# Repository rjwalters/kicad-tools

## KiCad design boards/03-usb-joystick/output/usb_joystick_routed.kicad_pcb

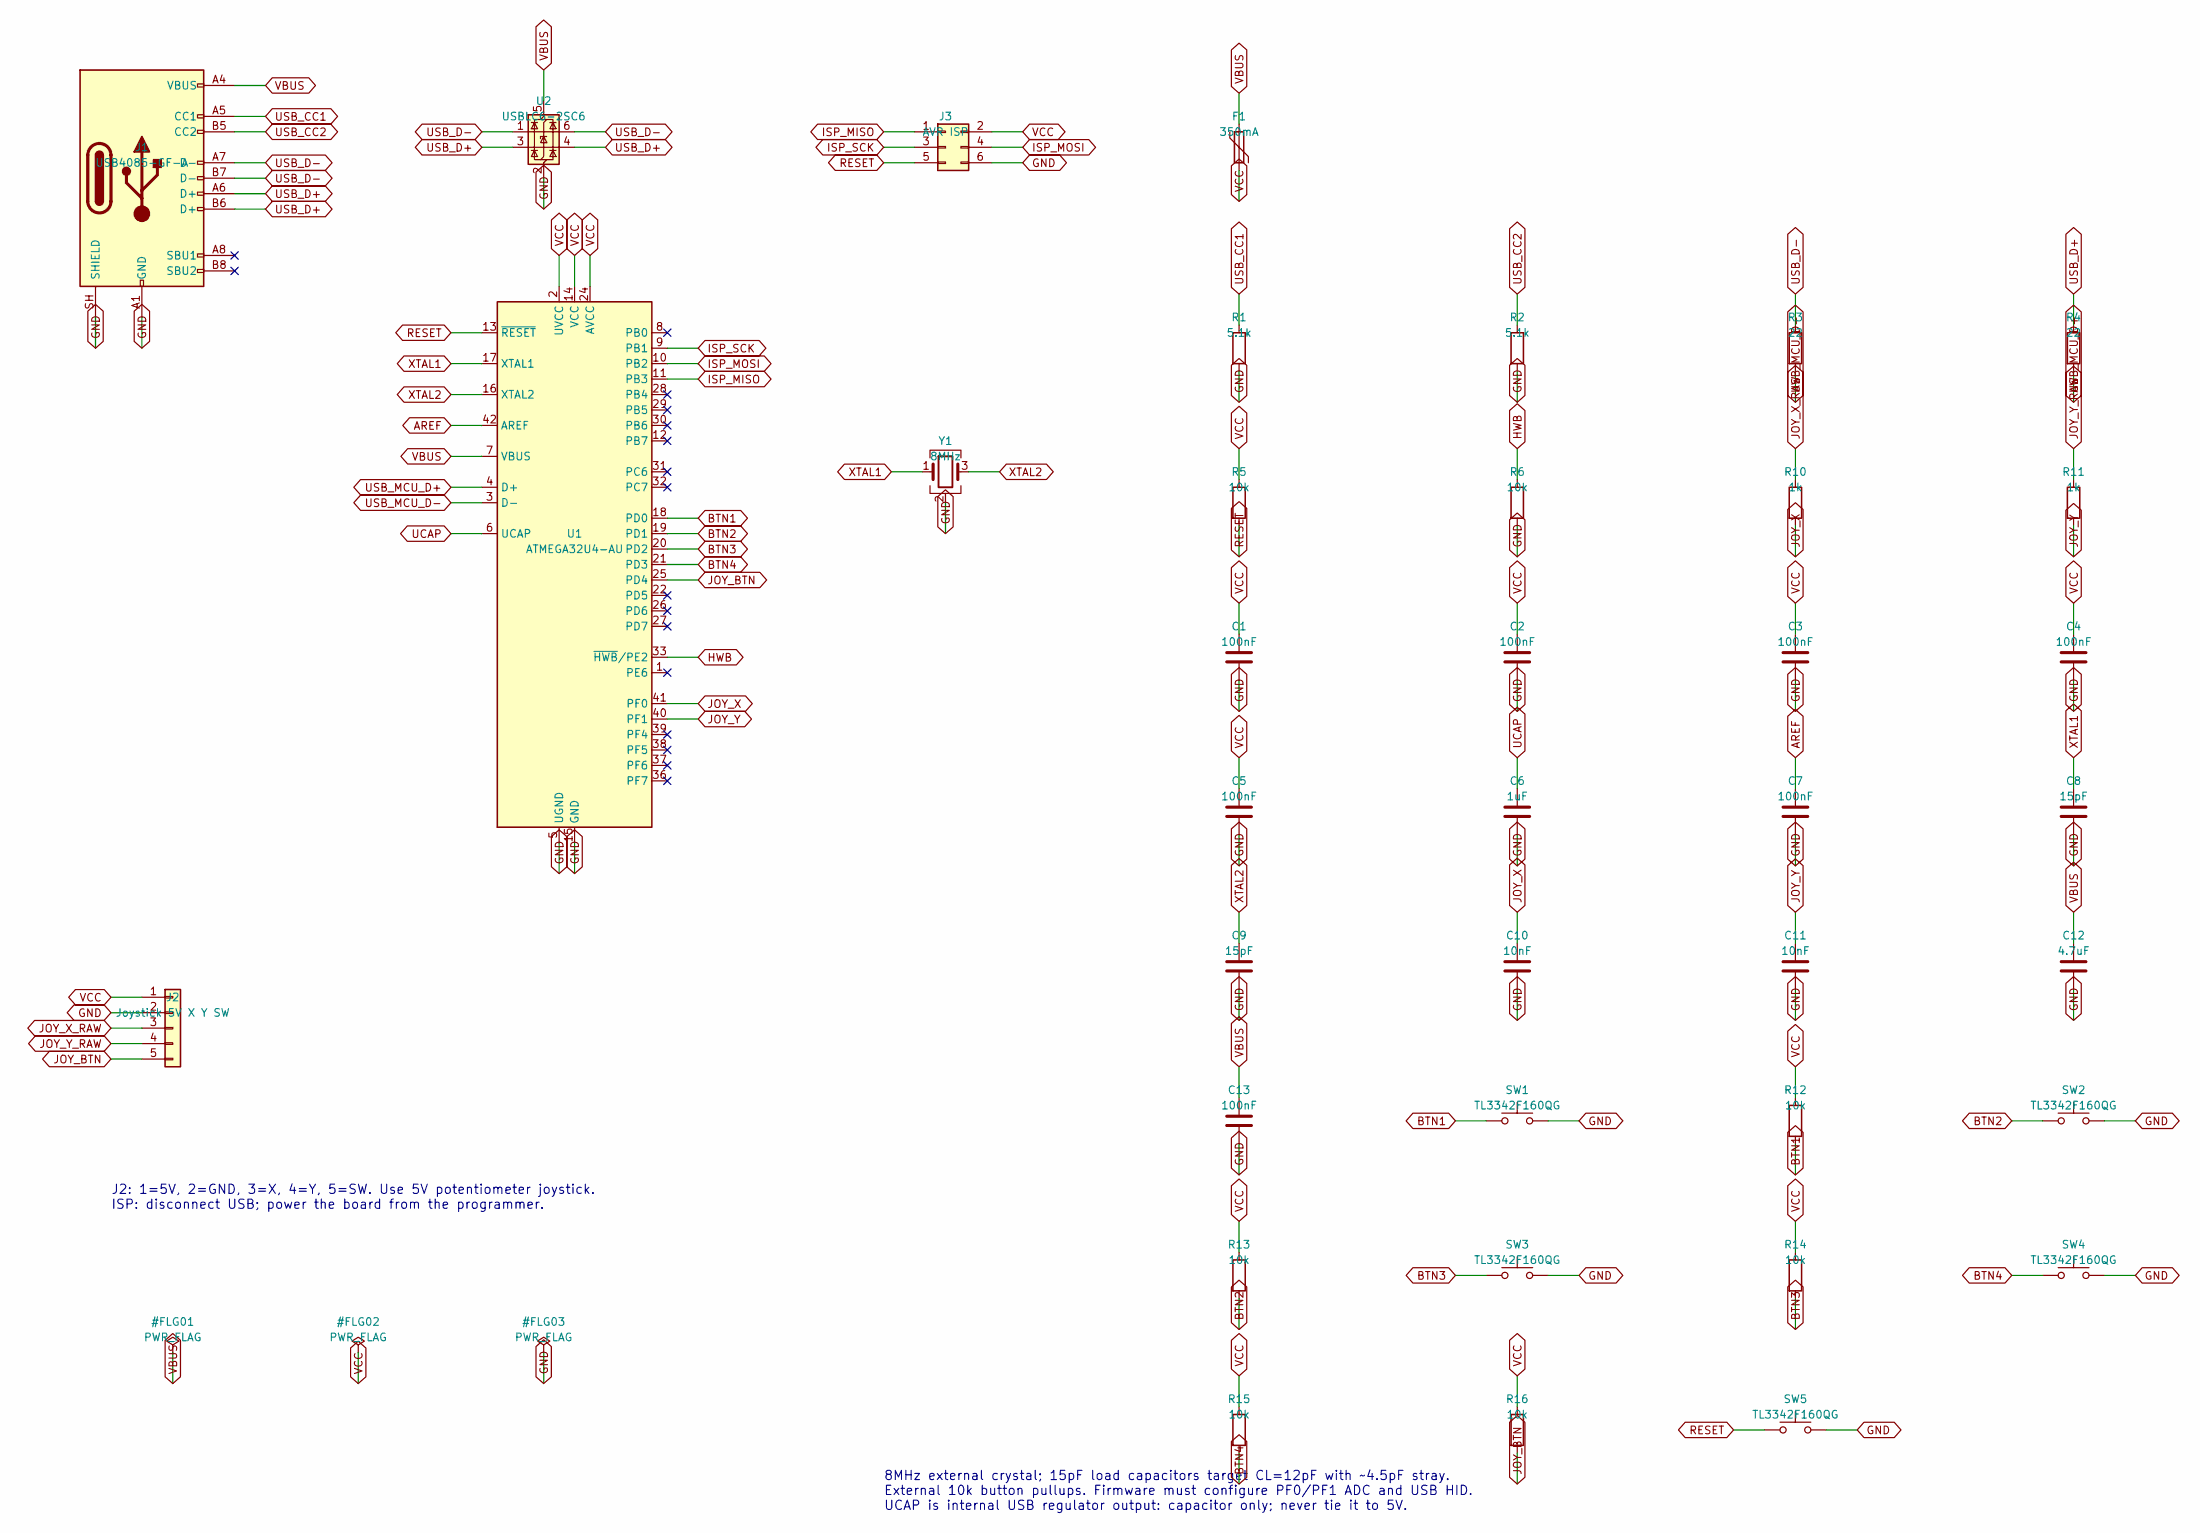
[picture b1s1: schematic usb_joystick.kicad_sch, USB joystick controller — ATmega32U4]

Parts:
C1, C2, C3, C4, C5, C7, C13: 100nF; C_0603_1608Metric; MPN GRM188R71C104KA01D; LCSC C45000
C6: 1uF; C_0603_1608Metric; MPN GRM188R71A105KA61D; LCSC C97888
C8, C9: 15pF; C_0603_1608Metric; MPN GRM1885C1H150JA01D; LCSC C71651
C10, C11: 10nF; C_0603_1608Metric; MPN GRM188R71H103KA01D; LCSC C77053
C12: 4.7uF; C_0603_1608Metric; MPN GRM188R61A475KE15D; LCSC C71633
F1: 350mA; Fuse_1206_3216Metric; MPN 1206L035/16YR; LCSC C126817
J1: USB4085-GF-A; USB_C_Receptacle_GCT_USB4085; MPN USB4085-GF-A; LCSC C7095263
J2: Joystick 5V X Y SW; JST_PH_S5B-PH-SM4-TB_1x05-1MP_P2.00mm_Horizontal; MPN S5B-PH-SM4-TB(LF)(SN); LCSC C265104
J3: AVR ISP; Samtec_TSM-103-01-T-DV; MPN TSM-103-01-T-DV-P-TR; LCSC C21285200
R1, R2: 5.1k; R_0603_1608Metric; MPN RC0603FR-075K1L; LCSC C105580
R3, R4: 22; R_0402_1005Metric; MPN RC0402FR-0722RL; LCSC C114765
R5, R6, R12, R13, R14, R15, R16: 10k; R_0603_1608Metric; MPN RC0603FR-0710KL; LCSC C98220
R10, R11: 1k; R_0603_1608Metric; MPN RC0603FR-071KL; LCSC C22548
SW1, SW2, SW3, SW4, SW5: TL3342F160QG; SW_SPST_TL3342; MPN TL3342F160QG; LCSC C2886898
U1: ATMEGA32U4-AU; TQFP-44_10x10mm_P0.8mm; MPN ATMEGA32U4-AU; LCSC C44854
U2: USBLC6-2SC6; SOT-23-6; MPN USBLC6-2SC6; LCSC C7519
Y1: 8MHz; Crystal_SMD_3225-4Pin_3.2x2.5mm; MPN ECS-80-12-33-JGN-TR; LCSC C2442665

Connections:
AREF: C7.1, U1.42 (AREF)
BTN1: R12.2, SW1.1, U1.18 (PD0)
BTN2: R13.2, SW2.1, U1.19 (PD1)
BTN3: R14.2, SW3.1, U1.20 (PD2)
BTN4: R15.2, SW4.1, U1.21 (PD3)
GND: C1.2, C2.2, C3.2, C4.2, C5.2, C6.2, C7.2, C8.2, C9.2, C10.2, C11.2, C12.2, C13.2, J1.A1 (GND), J1.A12 (GND), J1.B1 (GND), J1.B12 (GND), J1.SH (SHIELD), J2.2, J3.6, R1.2, R2.2, R6.2, SW1.2, SW2.2, SW3.2, SW4.2, SW5.2, U1.5 (UGND), U1.15 (GND), U1.23 (GND), U1.35 (GND), U1.43 (GND), U2.2 (GND), Y1.2 (G), Y1.4 (G)
HWB: R6.1, U1.33 (~HWB/PE2)
ISP_MISO: J3.1, U1.11 (PB3)
ISP_MOSI: J3.4, U1.10 (PB2)
ISP_SCK: J3.3, U1.9 (PB1)
JOY_BTN: J2.5, R16.2, U1.25 (PD4)
JOY_X: C10.1, R10.2, U1.41 (PF0)
JOY_X_RAW: J2.3, R10.1
JOY_Y: C11.1, R11.2, U1.40 (PF1)
JOY_Y_RAW: J2.4, R11.1
RESET: J3.5, R5.2, SW5.1, U1.13 (~RESET)
UCAP: C6.1, U1.6 (UCAP)
USB_CC1: J1.A5 (CC1), R1.1
USB_CC2: J1.B5 (CC2), R2.1
USB_D+: J1.A6 (D+), J1.B6 (D+), R4.1, U2.3 (I/O2), U2.4 (I/O2)
USB_D-: J1.A7 (D-), J1.B7 (D-), R3.1, U2.1 (I/O1), U2.6 (I/O1)
USB_MCU_D+: R4.2, U1.4 (D+)
USB_MCU_D-: R3.2, U1.3 (D-)
VBUS: C12.1, C13.1, F1.1, J1.A4 (VBUS), J1.A9 (VBUS), J1.B4 (VBUS), J1.B9 (VBUS), U1.7 (VBUS), U2.5 (VBUS)
VCC: C1.1, C2.1, C3.1, C4.1, C5.1, F1.2, J2.1, J3.2, R5.1, R12.1, R13.1, R14.1, R15.1, R16.1, U1.2 (UVCC), U1.14 (VCC), U1.24 (AVCC), U1.34 (VCC), U1.44 (AVCC)
XTAL1: C8.1, U1.17 (XTAL1), Y1.1
XTAL2: C9.1, U1.16 (XTAL2), Y1.3

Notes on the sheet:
J2: 1=5V, 2=GND, 3=X, 4=Y, 5=SW. Use 5V potentiometer joystick. ISP: disconnect USB; power the board from the programmer.
8MHz external crystal; 15pF load capacitors target CL=12pF with ~4.5pF stray. External 10k button pullups. Firmware must configure PF0/PF1 ADC and USB HID. UCAP is internal USB regulator output: capacitor only; never tie it to 5V.

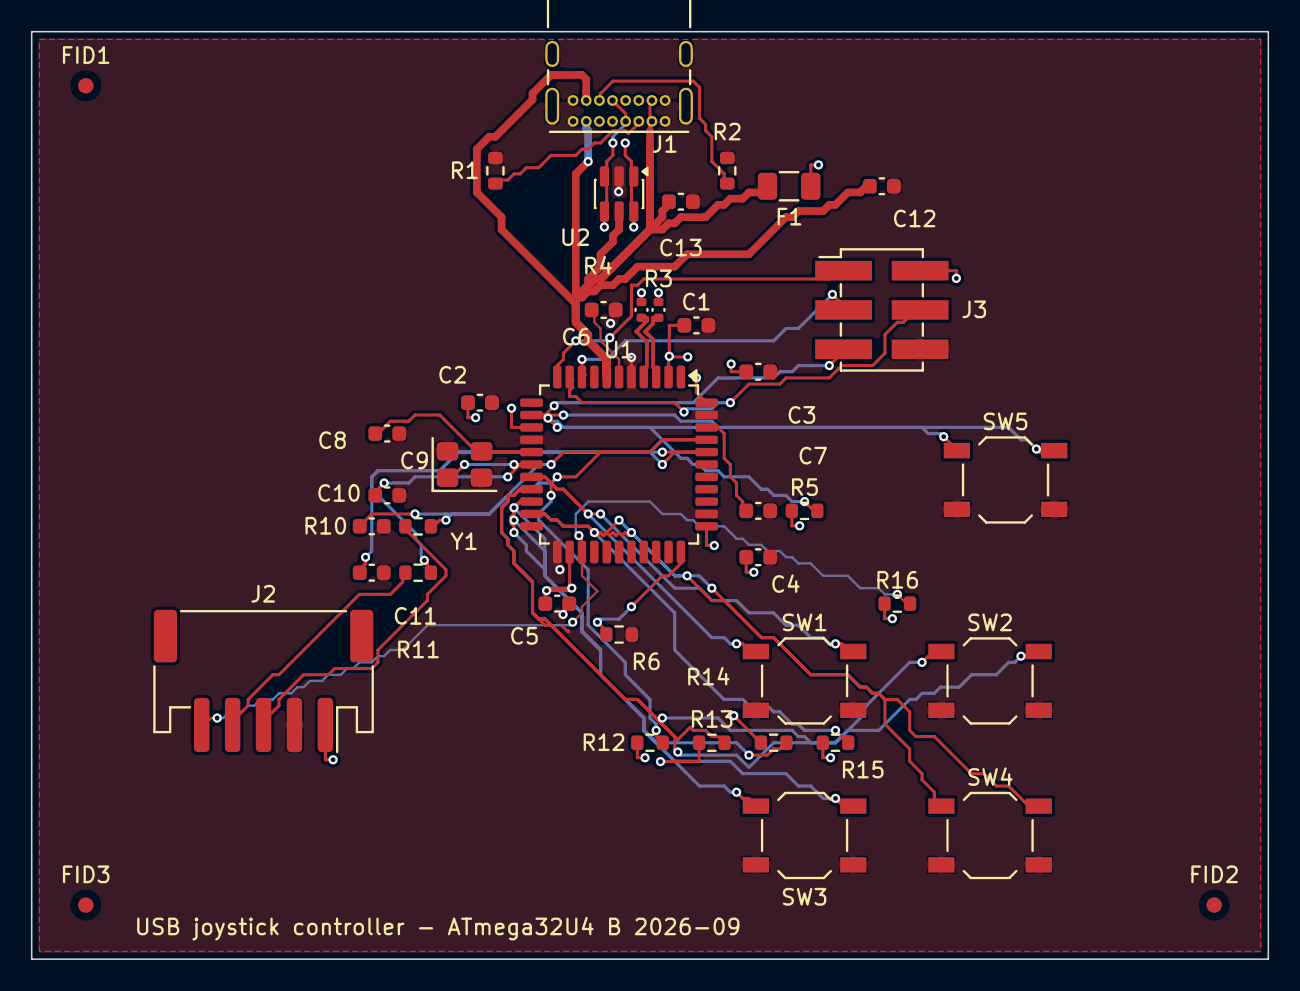
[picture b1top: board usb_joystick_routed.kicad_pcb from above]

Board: 4 copper layers, 80.0 x 60.0 mm, 41 parts (0 on the bottom side), 27 nets.

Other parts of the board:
FID1, FID2, FID3: Fiducial; Fiducial_1mm_Mask2mm

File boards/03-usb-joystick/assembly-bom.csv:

Reference,Value,Manufacturer,MPN,Footprint
U1,ATMEGA32U4-AU,Microchip,ATMEGA32U4-AU,Package_QFP:TQFP-44_10x10mm_P0.8mm
J1,USB4085-GF-A,GCT,USB4085-GF-A,Connector_USB:USB_C_Receptacle_GCT_USB4085
U2,USBLC6-2SC6,STMicroelectronics,USBLC6-2SC6,Package_TO_SOT_SMD:SOT-23-6
F1,350mA,Littelfuse,1206L035/16YR,Fuse:Fuse_1206_3216Metric
Y1,8MHz,ECS,ECS-80-12-33-JGN-TR,Crystal:Crystal_SMD_3225-4Pin_3.2x2.5mm
J2,Joystick 5V X Y SW,JST,S5B-PH-SM4-TB(LF)(SN),Connector_JST:JST_PH_S5B-PH-SM4-TB_1x05-1MP_P2.00mm_Horizontal
J3,AVR ISP,Samtec,TSM-103-01-T-DV-P-TR,Joystick:Samtec_TSM-103-01-T-DV
R1,5.1k,Yageo,RC0603FR-075K1L,Resistor_SMD:R_0603_1608Metric
R2,5.1k,Yageo,RC0603FR-075K1L,Resistor_SMD:R_0603_1608Metric
R3,22,Yageo,RC0402FR-0722RL,Resistor_SMD:R_0402_1005Metric
R4,22,Yageo,RC0402FR-0722RL,Resistor_SMD:R_0402_1005Metric
R5,10k,Yageo,RC0603FR-0710KL,Resistor_SMD:R_0603_1608Metric
R6,10k,Yageo,RC0603FR-0710KL,Resistor_SMD:R_0603_1608Metric
R10,1k,Yageo,RC0603FR-071KL,Resistor_SMD:R_0603_1608Metric
R11,1k,Yageo,RC0603FR-071KL,Resistor_SMD:R_0603_1608Metric
C1,100nF,Murata,GRM188R71C104KA01D,Capacitor_SMD:C_0603_1608Metric
C2,100nF,Murata,GRM188R71C104KA01D,Capacitor_SMD:C_0603_1608Metric
C3,100nF,Murata,GRM188R71C104KA01D,Capacitor_SMD:C_0603_1608Metric
C4,100nF,Murata,GRM188R71C104KA01D,Capacitor_SMD:C_0603_1608Metric
C5,100nF,Murata,GRM188R71C104KA01D,Capacitor_SMD:C_0603_1608Metric
C6,1uF,Murata,GRM188R71A105KA61D,Capacitor_SMD:C_0603_1608Metric
C7,100nF,Murata,GRM188R71C104KA01D,Capacitor_SMD:C_0603_1608Metric
C8,15pF,Murata,GRM1885C1H150JA01D,Capacitor_SMD:C_0603_1608Metric
C9,15pF,Murata,GRM1885C1H150JA01D,Capacitor_SMD:C_0603_1608Metric
C10,10nF,Murata,GRM188R71H103KA01D,Capacitor_SMD:C_0603_1608Metric
C11,10nF,Murata,GRM188R71H103KA01D,Capacitor_SMD:C_0603_1608Metric
C12,4.7uF,Murata,GRM188R61A475KE15D,Capacitor_SMD:C_0603_1608Metric
C13,100nF,Murata,GRM188R71C104KA01D,Capacitor_SMD:C_0603_1608Metric
SW1,TL3342F160QG,E-Switch,TL3342F160QG,Button_Switch_SMD:SW_SPST_TL3342
R12,10k,Yageo,RC0603FR-0710KL,Resistor_SMD:R_0603_1608Metric
SW2,TL3342F160QG,E-Switch,TL3342F160QG,Button_Switch_SMD:SW_SPST_TL3342
R13,10k,Yageo,RC0603FR-0710KL,Resistor_SMD:R_0603_1608Metric
SW3,TL3342F160QG,E-Switch,TL3342F160QG,Button_Switch_SMD:SW_SPST_TL3342
R14,10k,Yageo,RC0603FR-0710KL,Resistor_SMD:R_0603_1608Metric
SW4,TL3342F160QG,E-Switch,TL3342F160QG,Button_Switch_SMD:SW_SPST_TL3342
R15,10k,Yageo,RC0603FR-0710KL,Resistor_SMD:R_0603_1608Metric
R16,10k,Yageo,RC0603FR-0710KL,Resistor_SMD:R_0603_1608Metric
SW5,TL3342F160QG,E-Switch,TL3342F160QG,Button_Switch_SMD:SW_SPST_TL3342

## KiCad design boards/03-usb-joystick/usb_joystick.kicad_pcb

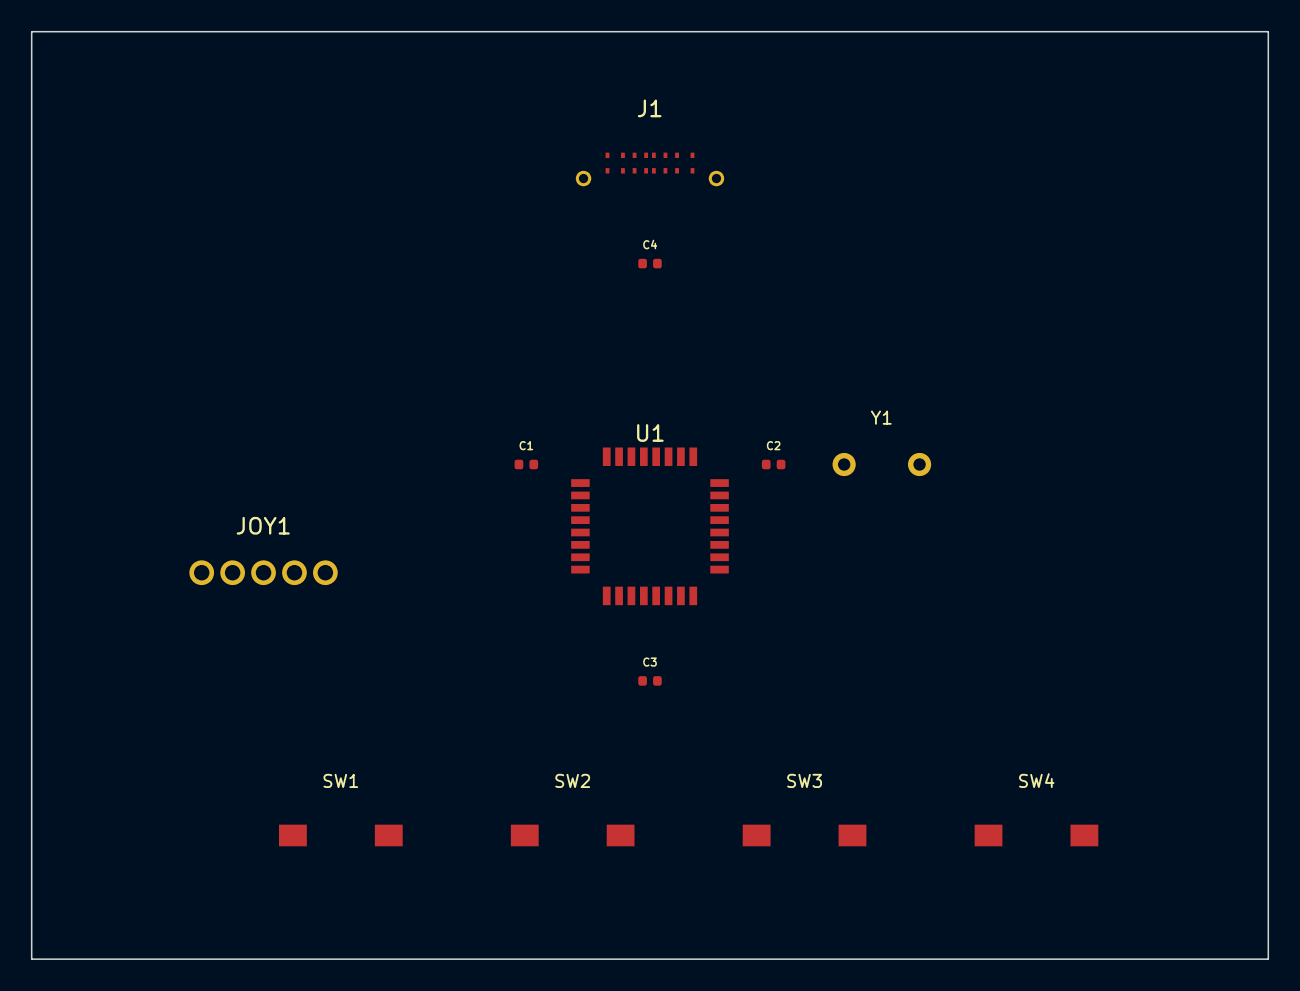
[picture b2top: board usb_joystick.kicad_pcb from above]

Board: 2 copper layers, 80.0 x 60.0 mm, 12 parts (0 on the bottom side), 16 nets, no tracks yet.

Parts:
C1, C2, C3, C4: 100nF; C_0402_1005Metric
J1: USB-C; USB_C_Receptacle_GCT_USB4105
JOY1: Joystick; Joystick_Analog
SW1, SW2, SW3, SW4: Button; SW_SPST_TL3342
U1: MCU; TQFP-32_7x7mm_P0.8mm
Y1: 16MHz; Crystal_HC49-U_Vertical

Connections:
BTN1: SW1.1, U1.12
BTN2: SW2.1, U1.13
BTN3: SW3.1, U1.14
BTN4: SW4.1, U1.15
GND: C1.2, C2.2, C3.2, C4.2, J1.A1, J1.A12, J1.B1, J1.B12, J1.S1, J1.S2, JOY1.1, SW1.2, SW2.2, SW3.2, SW4.2, U1.1, U1.7, U1.16, U1.23, U1.25, U1.32
JOY_BTN: JOY1.5, U1.11
JOY_X: JOY1.3, U1.9
JOY_Y: JOY1.4, U1.10
USB_CC1: J1.A5, U1.27
USB_CC2: J1.B5, U1.26
USB_D+: J1.A6, J1.B6, U1.29
USB_D-: J1.A7, J1.B7, U1.28
VBUS: C4.1, J1.A4, J1.A9, J1.B4, J1.B9, U1.30
VCC: C1.1, C2.1, C3.1, JOY1.2, U1.4, U1.8, U1.17, U1.24
XTAL1: U1.2, Y1.1
XTAL2: U1.3, Y1.2

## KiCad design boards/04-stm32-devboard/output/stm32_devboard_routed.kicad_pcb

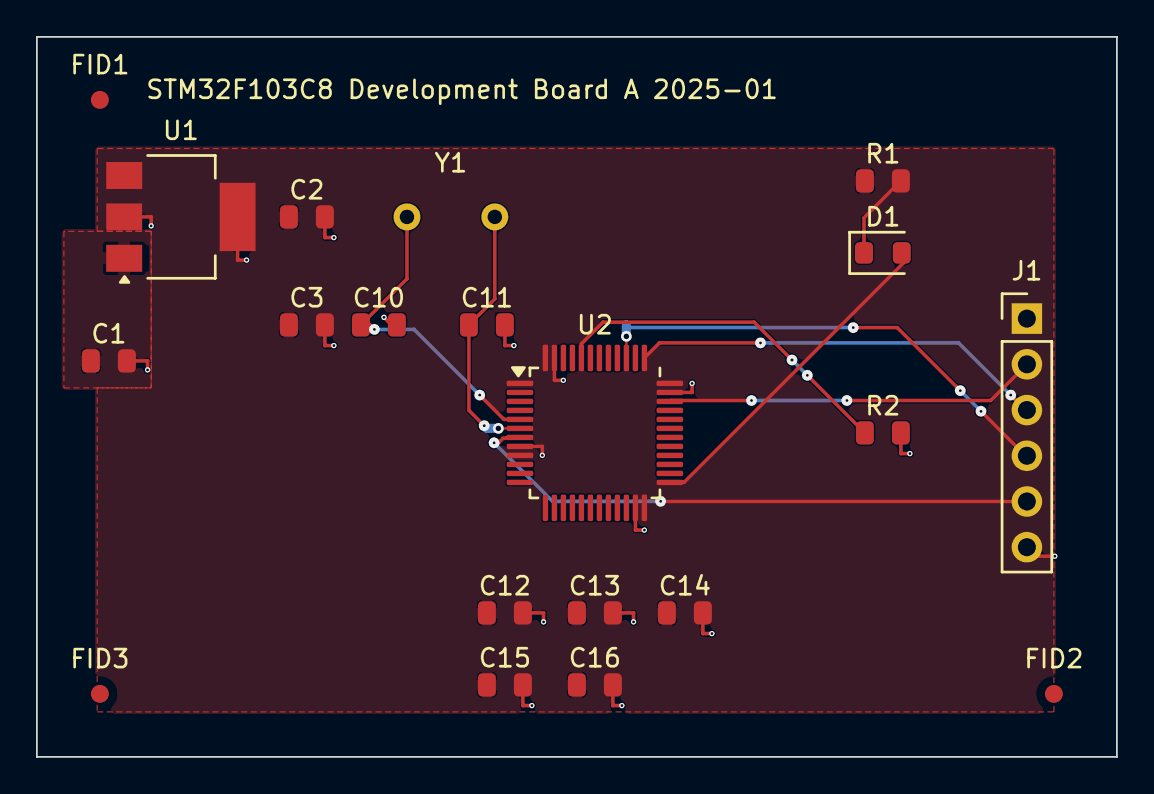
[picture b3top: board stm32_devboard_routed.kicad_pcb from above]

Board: 2 copper layers, 60.0 x 40.0 mm, 20 parts (0 on the bottom side), 12 nets.

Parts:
C1, C2: 10uF; C_0805_2012Metric
C3, C12, C13, C14, C15: 100nF; C_0805_2012Metric
C10, C11: 20pF; C_0805_2012Metric
C16: 4.7uF; C_0805_2012Metric
D1: LED; LED_0805_2012Metric
FID1, FID2, FID3: Fiducial; Fiducial_1mm_Mask2mm
J1: SWD-6; PinHeader_1x06_P2.54mm_Vertical
R1: 330R; R_0805_2012Metric
R2: 10k; R_0805_2012Metric
U1: MCP1825S-3302E/DB; SOT-223-3_TabPin2
U2: STM32F103C8T6; LQFP-48_7x7mm_P0.5mm
Y1: 8MHz; Crystal_HC49-4H_Vertical

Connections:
+3.3V: C2.1, C3.1, C12.1, C13.1, C14.1, C15.1, C16.1, J1.1, R1.1, U1.3 (VO), U2.1 (VBAT), U2.9 (VDDA), U2.24 (VDD), U2.36 (VDD), U2.48 (VDD)
+5V: C1.1, U1.1 (VI)
BOOT0: R2.1, U2.44 (BOOT0)
GND: C1.2, C2.2, C3.2, C10.2, C11.2, C12.2, C13.2, C14.2, C15.2, C16.2, J1.6, R2.2, U1.2 (GND), U2.8 (VSSA), U2.23 (VSS), U2.35 (VSS), U2.47 (VSS)
LED_K: D1.1 (K), R1.2
NRST: J1.5, U2.7 (NRST)
OSC_IN: C10.1, U2.5 (PD0), Y1.1
OSC_OUT: C11.1, U2.6 (PD1), Y1.2
SWCLK: J1.3, U2.37 (PA14)
SWDIO: J1.2, U2.34 (PA13)
SWO: J1.4, U2.39 (PB3)
USER_LED: D1.2 (A), U2.25 (PB12)

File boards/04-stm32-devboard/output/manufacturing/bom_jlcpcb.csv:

Comment,Designator,Footprint,LCSC Part #
100nF,"C12,C13,C14,C15,C3",Capacitor_SMD:C_0805_2012Metric,C49678
10k,R2,Resistor_SMD:R_0805_2012Metric,C17414
10uF,"C1,C2",Capacitor_SMD:C_0805_2012Metric,C15850
20pF,"C10,C11",Capacitor_SMD:C_0805_2012Metric,C1798
330R,R1,Resistor_SMD:R_0805_2012Metric,C17630
4.7uF,C16,Capacitor_SMD:C_0805_2012Metric,C1779
8MHz,Y1,Crystal:Crystal_HC49-4H_Vertical,C114147
LED,D1,LED_SMD:LED_0805_2012Metric,C131244
MCP1825S-3302E/DB,U1,Package_TO_SOT_SMD:SOT-223-3_TabPin2,C148031
STM32F103C8T6,U2,Package_QFP:LQFP-48_7x7mm_P0.5mm,C8734
SWD-6,J1,Connector_PinHeader_2.54mm:PinHeader_1x06_P2.54mm_Vertical,C37208

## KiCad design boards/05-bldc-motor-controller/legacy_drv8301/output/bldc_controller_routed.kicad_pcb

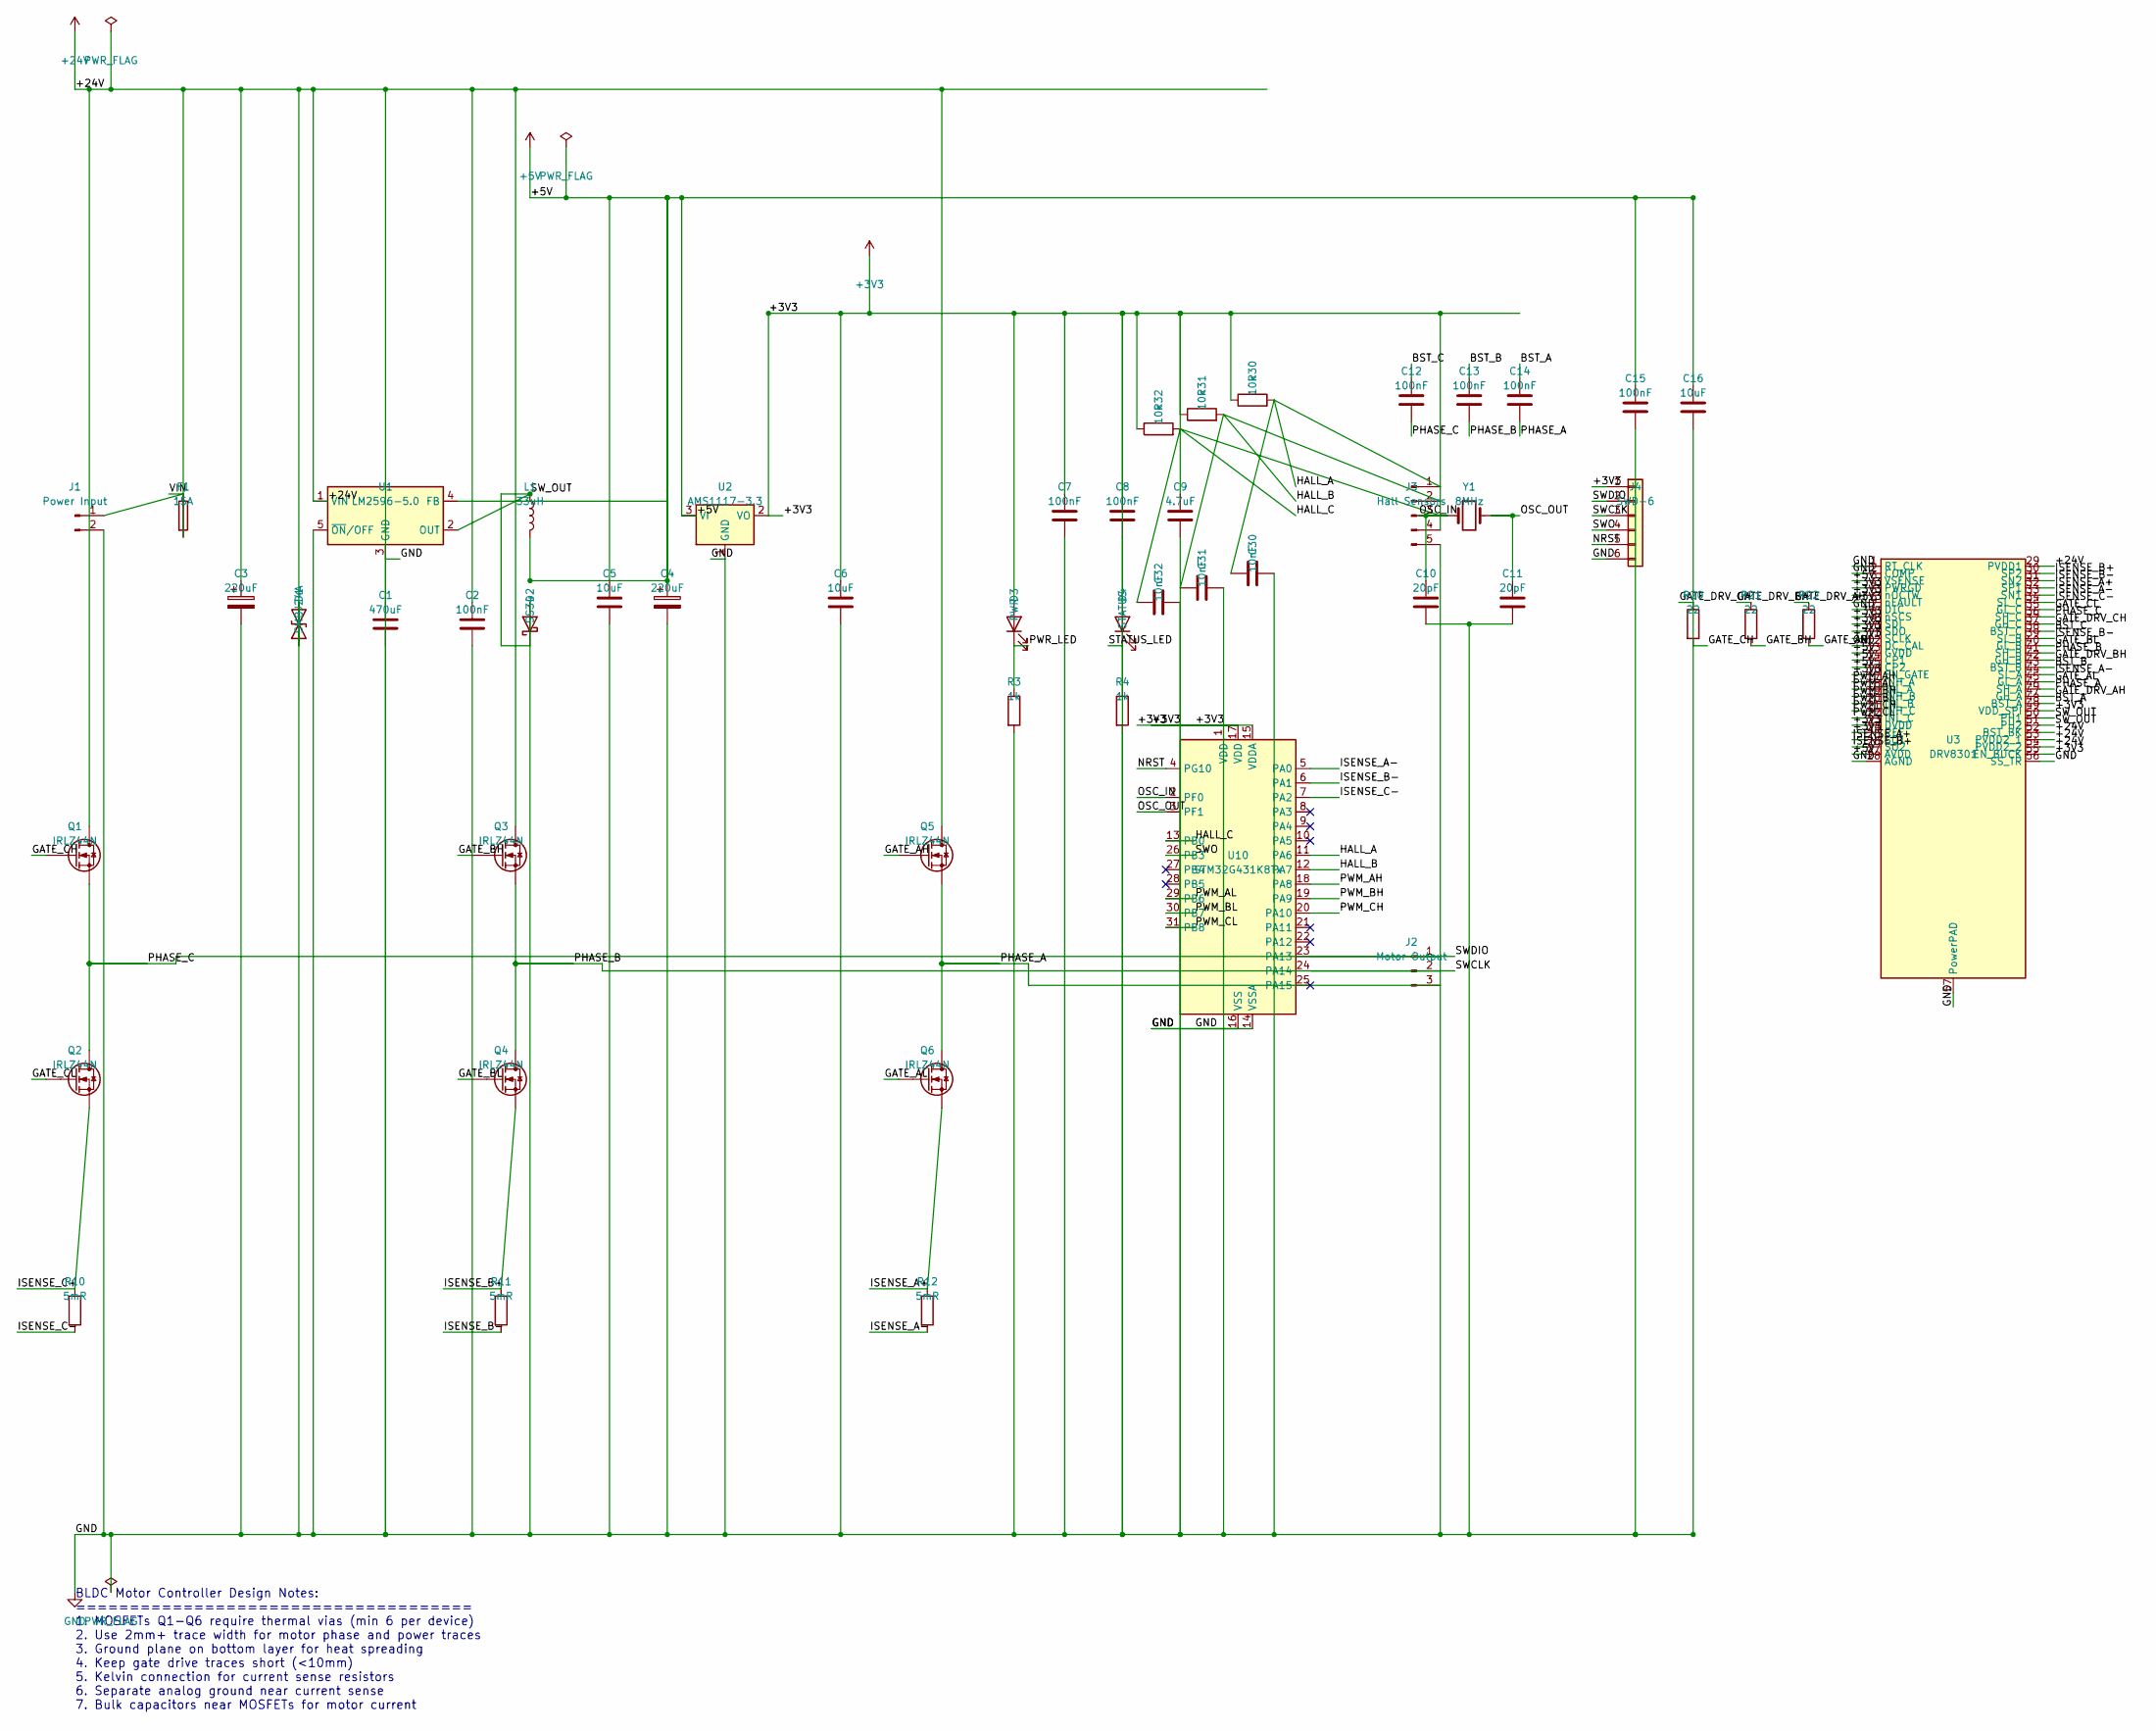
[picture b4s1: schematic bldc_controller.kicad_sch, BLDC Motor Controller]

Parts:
C1: 470uF; C_0805_2012Metric
C2, C7, C8, C12, C13, C14, C15: 100nF; C_0805_2012Metric
C3, C4: 220uF; C_0805_2012Metric
C5, C6, C16: 10uF; C_0805_2012Metric
C9: 4.7uF; C_0805_2012Metric
C10, C11: 20pF; C_0805_2012Metric
C30, C31, C32: 10nF; C_0805_2012Metric
D1: SMBJ24A; D_SMA
D2: SS34; D_SMA
D3: PWR; LED_0805_2012Metric
D4: STATUS; LED_0805_2012Metric
F1: 15A; Fuse_1206_3216Metric
J1: Power Input; PinHeader_1x02_P2.54mm_Vertical
J2: Motor Output; PinHeader_1x03_P2.54mm_Vertical
J3: Hall Sensors; PinHeader_1x05_P2.54mm_Vertical
J4: SWD-6; PinHeader_1x06_P2.54mm_Vertical
L1: 33uH; L_1210_3225Metric
Q1, Q2, Q3, Q4, Q5, Q6: IRLZ44N; TO-220-3_Vertical
R3, R4: 1k; R_0805_2012Metric
R10, R11, R12: 5mR; R_2512_6332Metric
R20, R21, R22: 22; R_0805_2012Metric
R30, R31, R32: 10k; R_0805_2012Metric
U1: LM2596-5.0; TO-263-5_TabPin3
U2: AMS1117-3.3; SOT-223-3_TabPin2
U3: DRV8301; HTSSOP-56-1EP_6.1x14mm_P0.5mm_EP3.61x6.35mm
U10: STM32G431K8Tx; LQFP-32_7x7mm_P0.8mm
Y1: 8MHz; Crystal_HC49-4H_Vertical

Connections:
+3V3: C6.1, C7.1, C8.1, C9.1, D3.2 (A), D4.2 (A), J3.4, J4.1, R30.1, R31.1, R32.1, U2.2 (VO), U3.4 (PWRGD), U3.5 (nOCTW), U3.6 (nFAULT), U3.8 (nSCS), U3.9 (SDI), U3.10 (SDO), U3.11 (SCLK), U3.16 (EN_GATE), U3.23 (DVDD), U3.24 (REF), U3.49 (VDD_SPI), U3.55 (EN_BUCK), U10.1 (VDD), U10.15 (VDDA), U10.17 (VDD)
BST_A: C14.1, U3.48 (BST_A)
BST_B: C13.1, U3.43 (BST_B)
BST_C: C12.1, U3.38 (BST_C)
GATE_AH: Q5.1 (G), R22.2
GATE_AL: Q6.1 (G), U3.45 (GL_A)
GATE_BH: Q3.1 (G), R21.2
GATE_BL: Q4.1 (G), U3.40 (GL_B)
GATE_CH: Q1.1 (G), R20.2
GATE_CL: Q2.1 (G), U3.35 (GL_C)
GATE_DRV_AH: R22.1, U3.47 (GH_A)
GATE_DRV_BH: R21.1, U3.42 (GH_B)
GATE_DRV_CH: R20.1, U3.37 (GH_C)
HALL_A: C30.1, J3.1, R30.2, U10.11 (PA6)
HALL_B: C31.1, J3.2, R31.2, U10.12 (PA7)
HALL_C: C32.1, J3.3, R32.2, U10.13 (PB0)
ISENSE_A+: Q6.3 (S), R12.1, U3.25 (SO1), U3.32 (SP1)
ISENSE_A-: R12.2, U3.33 (SN1), U3.44 (SL_A), U10.5 (PA0)
ISENSE_B+: Q4.3 (S), R11.1, U3.26 (SO2), U3.30 (SP2)
ISENSE_B-: R11.2, U3.31 (SN2), U3.39 (SL_B), U10.6 (PA1)
ISENSE_C+: Q2.3 (S), R10.1
ISENSE_C-: R10.2, U3.34 (SL_C), U10.7 (PA2)
NRST: J4.5, U10.4 (PG10)
OSC_IN: C10.1, U10.2 (PF0), Y1.1
OSC_OUT: C11.1, U10.3 (PF1), Y1.2
PHASE_A: C14.2, J2.3, Q5.3 (S), Q6.2 (D), U3.46 (SH_A)
PHASE_B: C13.2, J2.2, Q3.3 (S), Q4.2 (D), U3.41 (SH_B)
PHASE_C: C12.2, J2.1, Q1.3 (S), Q2.2 (D), U3.36 (SH_C)
PWM_AH: U3.17 (INH_A), U10.18 (PA8)
PWM_AL: U3.18 (INL_A), U10.29 (PB6)
PWM_BH: U3.19 (INH_B), U10.19 (PA9)
PWM_BL: U3.20 (INL_B), U10.30 (PB7)
PWM_CH: U3.21 (INH_C), U10.20 (PA10)
PWM_CL: U3.22 (INL_C), U10.31 (PB8)
PWR_LED: D3.1 (K), R3.1
STATUS_LED: D4.1 (K), R4.1
SWCLK: J4.3, U10.24 (PA14)
SWDIO: J4.2, U10.23 (PA13)
SWO: J4.4, U10.26 (PB3)
SW_OUT: D2.1 (K), L1.1, U1.2 (OUT), U3.50 (PH1), U3.51 (PH2)
VIN: F1.1, J1.1

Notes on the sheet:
BLDC Motor Controller Design Notes: ===================================== 1. MOSFETs Q1-Q6 require thermal vias (min 6 per device) 2. Use 2mm+ trace width for motor phase and power traces 3. Ground plane on bottom layer for heat spreading 4. Keep gate drive traces short (<10mm) 5. Kelvin connection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

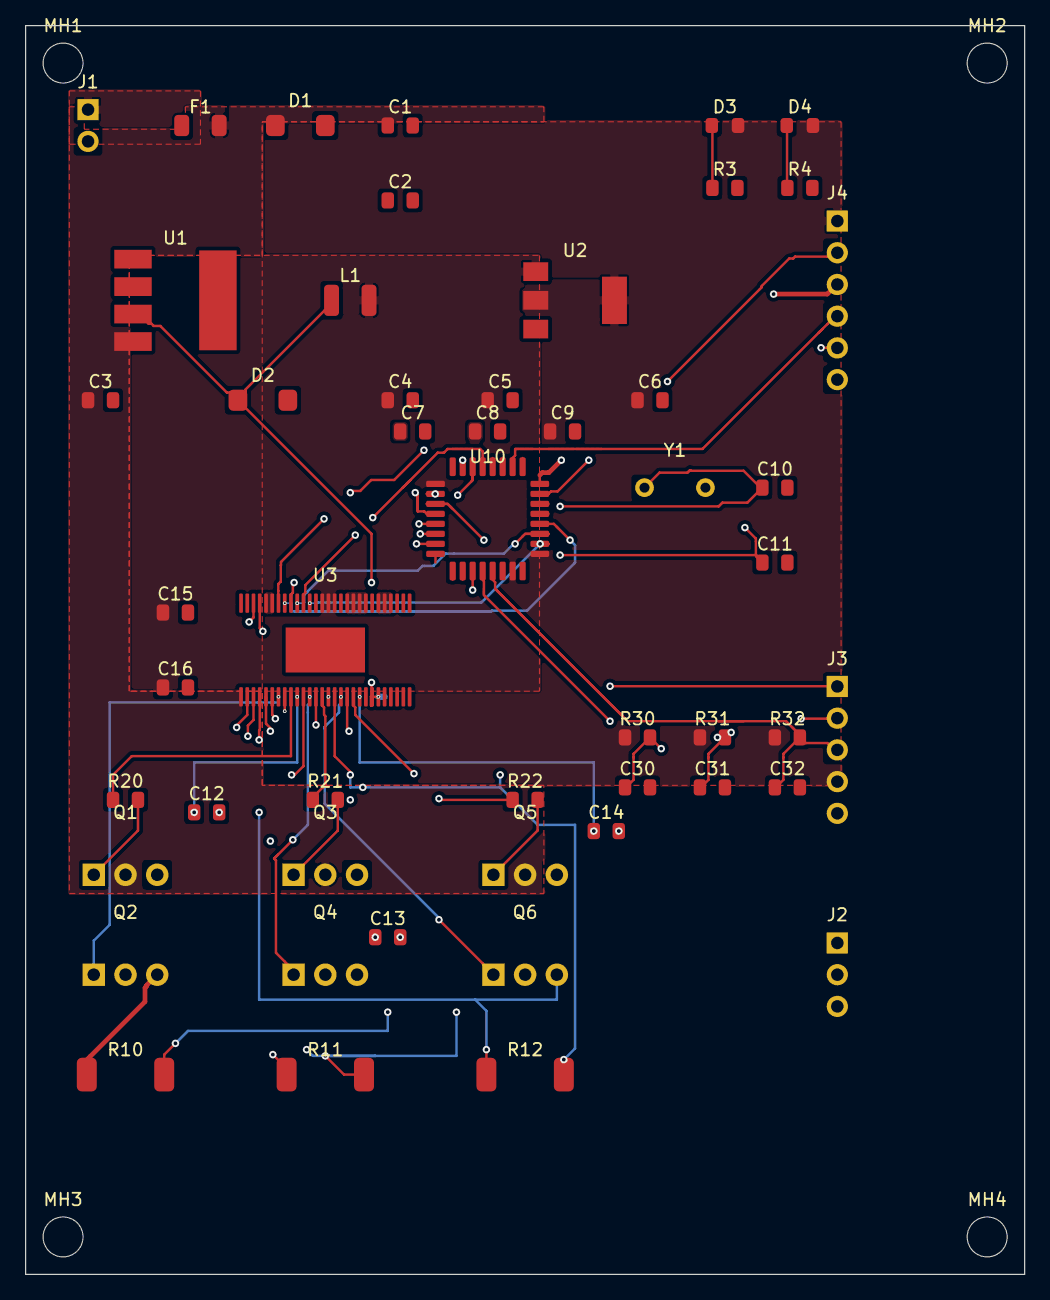
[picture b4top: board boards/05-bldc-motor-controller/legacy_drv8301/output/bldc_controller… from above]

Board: 4 copper layers, 80.0 x 100.0 mm, 55 parts (0 on the bottom side), 44 nets.

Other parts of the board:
MH1, MH2, MH3, MH4: MountingHole; MountingHole_3.2mm_M3
